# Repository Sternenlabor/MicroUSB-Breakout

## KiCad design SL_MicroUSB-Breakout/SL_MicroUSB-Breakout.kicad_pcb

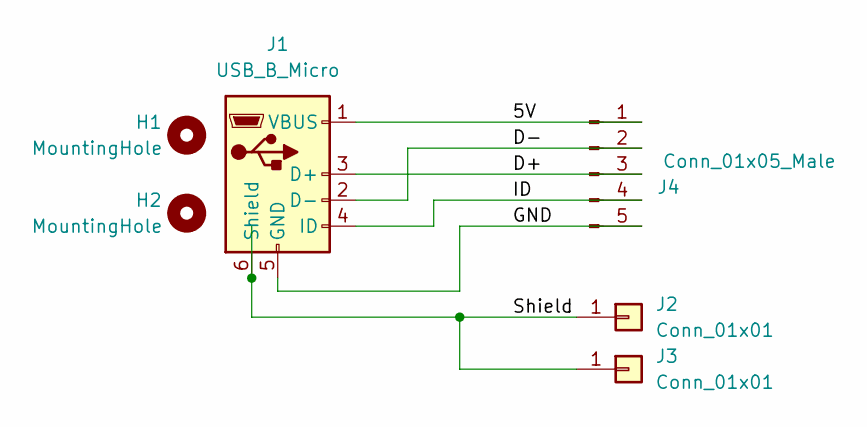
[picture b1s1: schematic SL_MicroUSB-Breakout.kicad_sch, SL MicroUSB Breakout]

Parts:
H1, H2: MountingHole; MountingHole_3.2mm_M3
J1: USB_B_Micro; USB_Micro-B_Molex-105017-0001
J2, J3: Conn_01x01; Pin_D1.0mm_L10.0mm
J4: Conn_01x05_Male; PinHeader_1x05_P2.54mm_Vertical

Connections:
/5V: J1.1 (VBUS), J4.1
/D+: J1.3 (D+), J4.3
/D-: J1.2 (D-), J4.2
/GND: J1.5 (GND), J4.5
/ID: J1.4 (ID), J4.4
/Shield: J1.6 (Shield), J2.1, J3.1

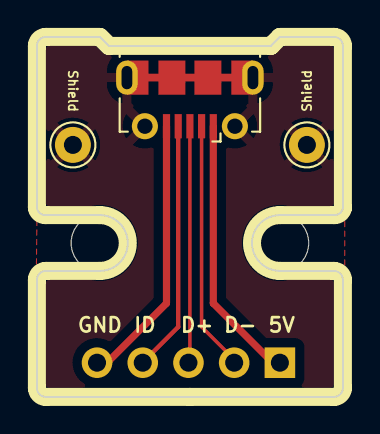
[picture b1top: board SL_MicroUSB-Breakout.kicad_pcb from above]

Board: 2 copper layers, 17.0 x 20.0 mm, 6 parts (1 on the bottom side), 6 nets.

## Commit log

2022-11-06 fix pin 1 marking
2024-02-23 added some notes
